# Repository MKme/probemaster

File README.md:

# ProbeMaster Breakout Board 
This board is to make my life easier when measuring/probing unknown hardware.  Often I want to hook up a logic probe or DMM in to the crcuit and manipulate the outputs- hence the dipswitches so I can turn things on or off

Buy a DIY kit in my store here: https://store.mkme.org/?product=probemaster-hardware-hacking-breakout-board

<p align="center">
<br>
 
 <br>

<br>
<br>
🐦 <a href="https://twitter.com/mkmeorg">Twitter</a>
| 📺 <a href="https://www.youtube.com/mkmeorg">YouTube</a>
| 🌍 <a href="http://www.mkme.org">mkme.org</a><br>
Support this project and become a patron on <a href="http://mkme.org/patreon">Eric's Patreon</a>.<br>
Website, Forum and store are at http://mkme.org <br>
Chat with Me: <a href="https://discord.gg/j9S4Fgv">Discord</a></b>
</p>

The protoyping area will allow me to add any components INSIDE the working crcuit while measuring on the DUT- Handy eh?

You can add capacitance, resistance, switches LED indicators easily by putting them right in series or parell with the circuit

While the DIPswitch conenctions allow probing the lower connections are not joined in the center- this allows the user to either connect them or conenct with more components as mentioned above

Forum Thread HERE - http://forum.mkme.org/viewtopic.php?f=5&t=1162

My Videos HERE: https://www.youtube.com/mkmeorg

# Hardware:

### Parts can be found in the KiCad BOM 

Buy the PCB in my store: https://store.mkme.org/?product=probemaster-hardware-hacking-breakout-board

Buy DIP switches on Amazon: https://amzn.to/2UbDWsz

Header pins colored : https://amzn.to/3euvvPY

Header pins black only https://amzn.to/3z3T4Xy 

# Project:

###  Base/Enclosure

While the initial design is off at PCBWay for board fab I decided to make a base to set the unit on.  

To do this I used Kicad Plot and exported the Drill file as SVG see file ProbeMaster-PTH-drl_map:

I pulled this in to Inkscape and just traced the outline and plotted 4 3mm mounting holes aligning them with the PCB holes

This I can use easily in my K40 laser cutter to cut a nice acrylic base.  

Kit: https://store.mkme.org/?product=probemaster-hardware-hacking-breakout-board

This work is licensed under a Creative Commons Attribution-NonCommercial 4.0 International License. https://creativecommons.org/licenses/by-nc/4.0/

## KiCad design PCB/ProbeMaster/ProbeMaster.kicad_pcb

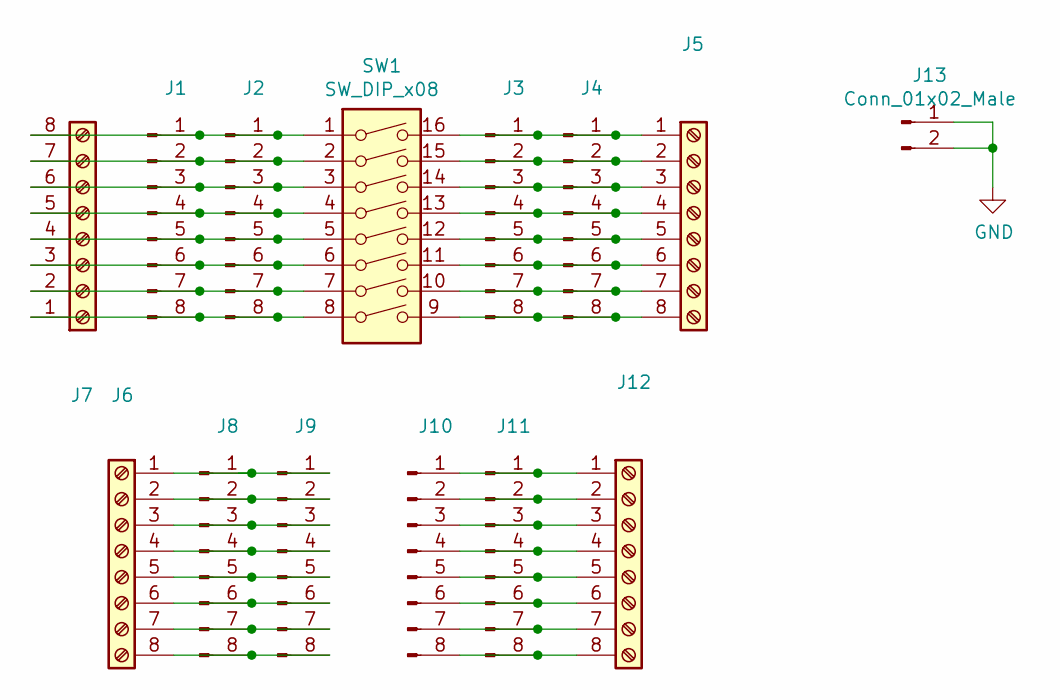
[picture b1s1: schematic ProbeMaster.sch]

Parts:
J1, J2, J3, J4, J8, J9, J10, J11: Conn_01x08_Male; PinHeader_1x08_P2.54mm_Vertical
J5, J6, J7, J12: Screw_Terminal_01x08; TerminalBlock_RND_205-00293_1x08_P5.08mm_Horizontal
J13: Conn_01x02_Male; PinHeader_1x02_P2.54mm_Vertical
SW1: SW_DIP_x08; DIP-16_W10.16mm

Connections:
unnamed: J1.1, J2.1, J7.8, SW1.1
unnamed: J1.2, J2.2, J7.7, SW1.2
unnamed: J1.3, J2.3, J7.6, SW1.3
unnamed: J1.4, J2.4, J7.5, SW1.4
unnamed: J1.5, J2.5, J7.4, SW1.5
unnamed: J1.6, J2.6, J7.3, SW1.6
unnamed: J1.7, J2.7, J7.2, SW1.7
unnamed: J1.8, J2.8, J7.1, SW1.8
unnamed: J3.1, J4.1, J5.1, SW1.16
unnamed: J3.2, J4.2, J5.2, SW1.15
unnamed: J3.3, J4.3, J5.3, SW1.14
unnamed: J3.4, J4.4, J5.4, SW1.13
unnamed: J3.5, J4.5, J5.5, SW1.12
unnamed: J3.6, J4.6, J5.6, SW1.11
unnamed: J3.7, J4.7, J5.7, SW1.10
unnamed: J3.8, J4.8, J5.8, SW1.9
unnamed: J6.1, J8.1, J9.1
unnamed: J6.2, J8.2, J9.2
unnamed: J6.3, J8.3, J9.3
unnamed: J6.4, J8.4, J9.4
unnamed: J6.5, J8.5, J9.5
unnamed: J6.6, J8.6, J9.6
unnamed: J6.7, J8.7, J9.7
unnamed: J6.8, J8.8, J9.8
unnamed: J10.1, J11.1, J12.1
unnamed: J10.2, J11.2, J12.2
unnamed: J10.3, J11.3, J12.3
unnamed: J10.4, J11.4, J12.4
unnamed: J10.5, J11.5, J12.5
unnamed: J10.6, J11.6, J12.6
unnamed: J10.7, J11.7, J12.7
unnamed: J10.8, J11.8, J12.8
unnamed: J13.1, J13.2

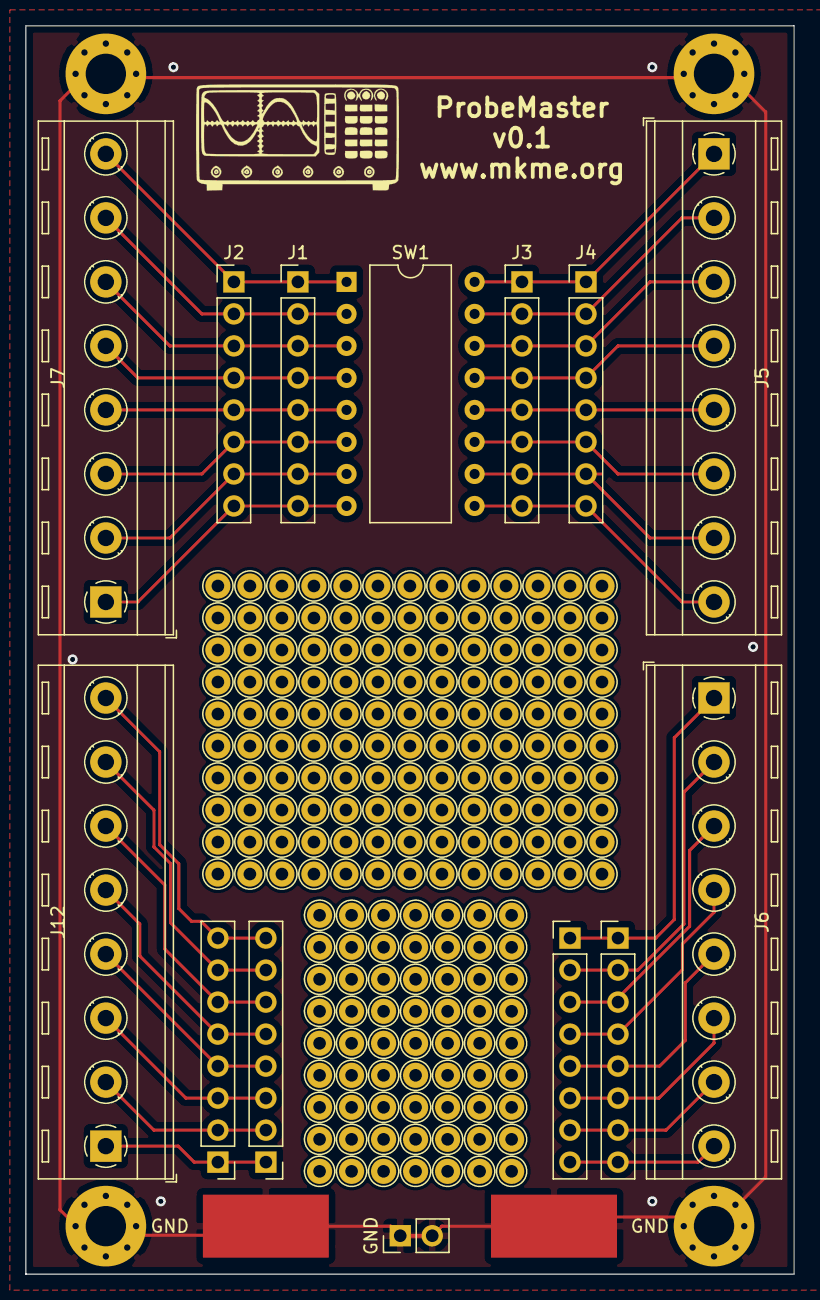
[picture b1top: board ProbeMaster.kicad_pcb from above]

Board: 2 copper layers, 61.0 x 99.1 mm, 15 parts (0 on the bottom side), 33 nets.

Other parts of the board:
GND: SolderWirePad_1x01_SMD_5x10mm
GND#2: Conn_01x02_Male; PinHeader_1x02_P2.54mm_Vertical

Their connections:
GND: GND.1, GND#2.1, GND#2.2

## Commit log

2021-07-16 ProbeMaster designed
2021-07-16 update edgecuts
2021-07-16 Pics
2021-07-18 Svgs for bottom plate
2021-08-10 Updated parts
2021-10-10 Photos and kit updated
